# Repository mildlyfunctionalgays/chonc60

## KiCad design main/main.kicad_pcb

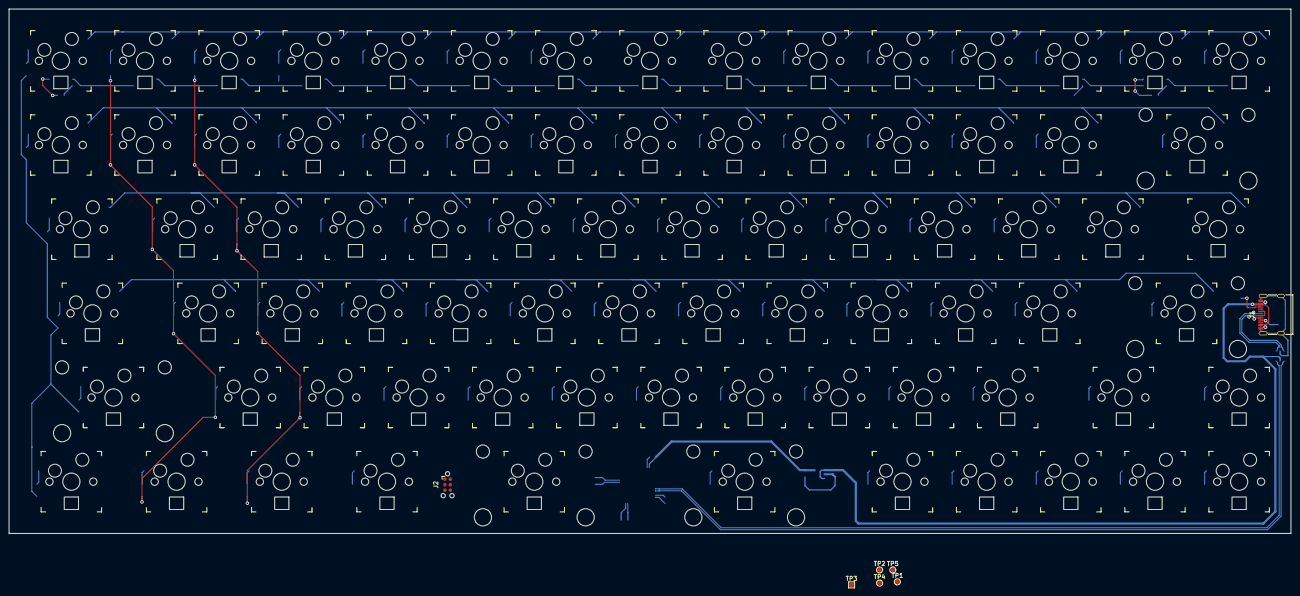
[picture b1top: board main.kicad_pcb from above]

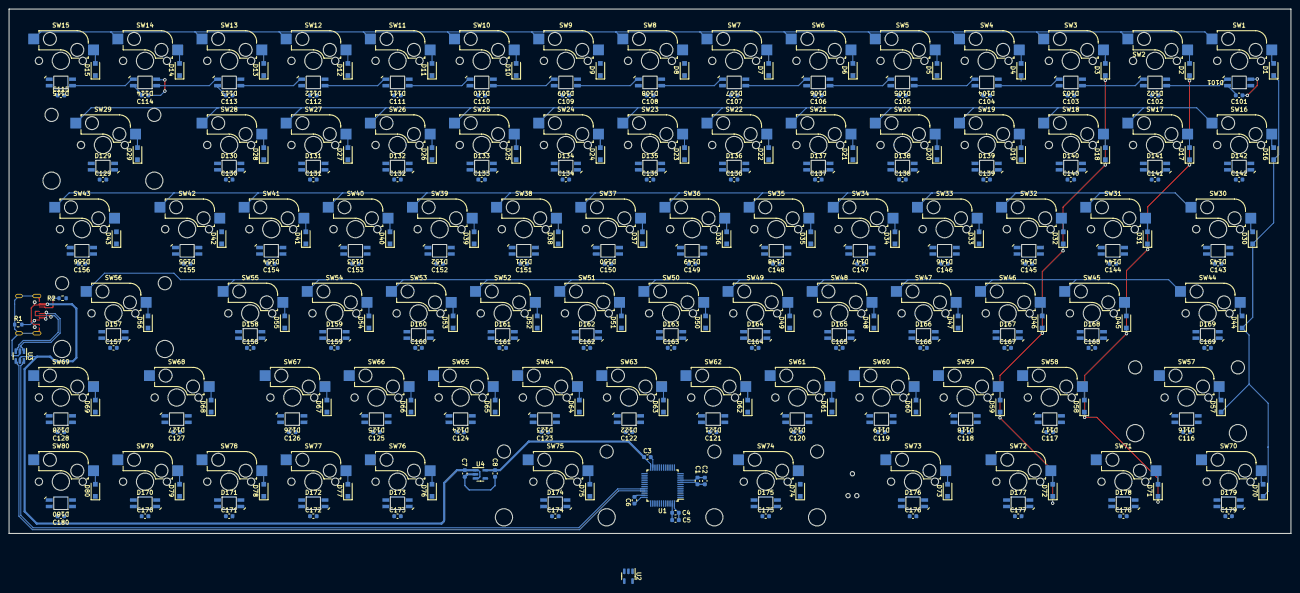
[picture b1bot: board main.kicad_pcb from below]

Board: 2 copper layers, 297.0 x 121.5 mm, 341 parts (254 on the bottom side), 195 nets.

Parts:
C1, C3, C4, C6, C101, C102, C103, C104, C105, C106, C107, C108, C109, C110, C111, C112, C113, C114, C115, C116, C117, C118, C119, C120, C121, C122, C123, C124, C125, C126, C127, C128, C129, C130, C131, C132, C133, C134, C135, C136, C137, C138, C139, C140, C141, C142, C143, C144, C145, C146, C147, C148, C149, C150, C151, C152, C153, C154, C155, C156, C157, C158, C159, C160, C161, C162, C163, C164, C165, C166, C167, C168, C169, C170, C171, C172, C173, C174, C175, C176, C177, C178, C179, C180: 100nF; C_0603_1608Metric
C2, C7, C8: 1µF; C_0603_1608Metric
C5: 10µF; C_0603_1608Metric
D1, D2, D3, D4, D5, D6, D7, D8, D9, D10, D11, D12, D13, D14, D15, D16, D17, D18, D19, D20, D21, D22, D23, D24, D25, D26, D27, D28, D29, D30, D31, D32, D33, D34, D35, D36, D37, D38, D39, D40, D41, D42, D43, D44, D45, D46, D47, D48, D49, D50, D51, D52, D53, D54, D55, D56, D57, D58, D59, D60, D61, D62, D63, D64, D65, D66, D67, D68, D69, D70, D71, D72, D73, D74, D75, D76, D77, D78, D79, D80: D_Small; D_SOD-123F
D101, D102, D103, D104, D105, D106, D107, D108, D109, D110, D111, D112, D113, D114, D115, D116, D117, D118, D119, D120, D121, D122, D123, D124, D125, D126, D127, D128, D129, D130, D131, D132, D133, D134, D135, D136, D137, D138, D139, D140, D141, D142, D143, D144, D145, D146, D147, D148, D149, D150, D151, D152, D153, D154, D155, D156, D157, D158, D159, D160, D161, D162, D163, D164, D165, D166, D167, D168, D169, D170, D171, D172, D173, D174, D175, D176, D177, D178, D179, D180: SK6812MINI-E; LED_SK6812_MINI_E_REVERSE
J1: USB_C_Receptacle_USB2.0; USB_C_Receptacle_JING_C167321
J2: TC2030_SWD; Tag-Connect_TC2030-IDC-NL_2x03_P1.27mm_Vertical
R1, R2: 5.1kΩ; R_0603_1608Metric
SW1, SW2, SW3, SW4, SW5, SW6, SW7, SW8, SW9, SW10, SW11, SW12, SW13, SW14, SW15, SW16, SW17, SW18, SW19, SW20, SW21, SW22, SW23, SW24, SW25, SW26, SW27, SW28, SW29, SW30, SW31, SW32, SW33, SW34, SW35, SW36, SW37, SW38, SW39, SW40, SW41, SW42, SW43, SW44, SW45, SW46, SW47, SW48, SW49, SW50, SW51, SW52, SW53, SW54, SW55, SW56, SW57, SW58, SW59, SW60, SW61, SW62, SW63, SW64, SW65, SW66, SW67, SW68, SW69, SW70, SW71, SW72, SW73, SW74, SW75, SW76, SW77, SW78, SW79, SW80: SW_Push_45deg; Kailh_socket_MX
TP1: BOOT0; TestPoint_Pad_D1.0mm
TP2: ~RESET; TestPoint_Pad_D1.0mm
TP3: GND; TestPoint_Pad_1.0x1.0mm
TP4: 5V; TestPoint_Pad_D1.0mm
TP5: 3V3; TestPoint_Pad_D1.0mm
U1: STM32L063C8Tx; LQFP-48_7x7mm_P0.5mm
U2: SN74LV1T34DBV; SOT-23-5
U3: WE-TVS-82400102; SOT-23-6
U4: MIC5504-3.3YMT; SOT-23-5

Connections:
+3V3: C1.1, C2.1, C3.1, C4.1, C5.1, C6.1, C8.1, J2.5 (GND), TP5.1, U1.9 (VDDA), U1.24 (VDD), U1.36 (VDD_USB), U1.48 (VDD), U4.5 (VOUT)
+5V: C7.1, C101.2, C102.2, C103.2, C104.2, C105.2, C106.2, C107.2, C108.2, C109.2, C110.2, C111.2, C112.2, C113.2, C114.2, C115.2, C116.2, C117.2, C118.2, C119.2, C120.2, C121.2, C122.2, C123.2, C124.2, C125.2, C126.2, C127.2, C128.2, C129.2, C130.2, C131.2, C132.2, C133.2, C134.2, C135.2, C136.2, C137.2, C138.2, C139.2, C140.2, C141.2, C142.2, C143.2, C144.2, C145.2, C146.2, C147.2, C148.2, C149.2, C150.2, C151.2, C152.2, C153.2, C154.2, C155.2, C156.2, C157.2, C158.2, C159.2, C160.2, C161.2, C162.2, C163.2, C164.2, C165.2, C166.2, C167.2, C168.2, C169.2, C170.2, C171.2, C172.2, C173.2, C174.2, C175.2, C176.2, C177.2, C178.2, C179.2, C180.2, D101.1 (VDD), D102.1 (VDD), D103.1 (VDD), D104.1 (VDD), D105.1 (VDD), D106.1 (VDD), D107.1 (VDD), D108.1 (VDD), D109.1 (VDD), D110.1 (VDD), D111.1 (VDD), D112.1 (VDD), D113.1 (VDD), D114.1 (VDD), D115.1 (VDD), D116.1 (VDD), D117.1 (VDD), D118.1 (VDD), D119.1 (VDD), D120.1 (VDD), D121.1 (VDD), D122.1 (VDD), D123.1 (VDD), D124.1 (VDD), D125.1 (VDD), D126.1 (VDD), D127.1 (VDD), D128.1 (VDD), D129.1 (VDD), D130.1 (VDD), D131.1 (VDD), D132.1 (VDD), D133.1 (VDD), D134.1 (VDD), D135.1 (VDD), D136.1 (VDD), D137.1 (VDD), D138.1 (VDD), D139.1 (VDD), D140.1 (VDD), D141.1 (VDD), D142.1 (VDD), D143.1 (VDD), D144.1 (VDD), D145.1 (VDD), D146.1 (VDD), D147.1 (VDD), D148.1 (VDD), D149.1 (VDD), D150.1 (VDD), D151.1 (VDD), D152.1 (VDD), D153.1 (VDD), D154.1 (VDD), D155.1 (VDD), D156.1 (VDD), D157.1 (VDD), D158.1 (VDD), D159.1 (VDD), D160.1 (VDD), D161.1 (VDD), D162.1 (VDD), D163.1 (VDD), D164.1 (VDD), D165.1 (VDD), D166.1 (VDD), D167.1 (VDD), D168.1 (VDD), D169.1 (VDD), D170.1 (VDD), D171.1 (VDD), D172.1 (VDD), D173.1 (VDD), D174.1 (VDD), D175.1 (VDD), D176.1 (VDD), D177.1 (VDD), D178.1 (VDD), D179.1 (VDD), D180.1 (VDD), J1.A4 (VBUS), J1.A9 (VBUS), J1.B4 (VBUS), J1.B9 (VBUS), TP4.1, U2.5 (VCC), U3.5, U4.1 (VIN), U4.3 (EN)
/C_D+: J1.A6 (D+), J1.B6 (D+), U3.3
/C_D-: J1.A7 (D-), J1.B7 (D-), U3.1
/Keyswitches/COL0: D1.1 (K), D16.1 (K), D30.1 (K), D44.1 (K), D57.1 (K), D70.1 (K), U1.10 (PA0)
/Keyswitches/COL1: D2.1 (K), D17.1 (K), D31.1 (K), D45.1 (K), D58.1 (K), D71.1 (K), U1.11 (PA1)
/Keyswitches/COL2: D3.1 (K), D18.1 (K), D32.1 (K), D46.1 (K), D59.1 (K), D72.1 (K), U1.12 (PA2)
/Keyswitches/COL3: D4.1 (K), D19.1 (K), D33.1 (K), D47.1 (K), D60.1 (K), D73.1 (K), U1.13 (PA3)
/Keyswitches/COL4: D5.1 (K), D20.1 (K), D34.1 (K), D48.1 (K), D61.1 (K), D74.1 (K), U1.14 (PA4)
/Keyswitches/COL5: D6.1 (K), D21.1 (K), D35.1 (K), D49.1 (K), D62.1 (K), U1.15 (PA5)
/Keyswitches/COL6: D7.1 (K), D22.1 (K), D36.1 (K), D50.1 (K), D63.1 (K), U1.16 (PA6)
/Keyswitches/COL7: D8.1 (K), D23.1 (K), D37.1 (K), D51.1 (K), D64.1 (K), D75.1 (K), U1.17 (PA7)
/Keyswitches/COL8: D9.1 (K), D24.1 (K), D38.1 (K), D52.1 (K), D65.1 (K), U1.18 (PB0)
/Keyswitches/COL9: D10.1 (K), D25.1 (K), D39.1 (K), D53.1 (K), U1.19 (PB1)
/Keyswitches/COL10: D11.1 (K), D26.1 (K), D40.1 (K), D76.1 (K), U1.20 (PB2)
/Keyswitches/COL11: D12.1 (K), D27.1 (K), D41.1 (K), D54.1 (K), D66.1 (K), D77.1 (K), U1.21 (PB10)
/Keyswitches/COL12: D13.1 (K), D28.1 (K), D42.1 (K), D55.1 (K), D67.1 (K), D78.1 (K), U1.22 (PB11)
/Keyswitches/COL13: D14.1 (K), D29.1 (K), D43.1 (K), D56.1 (K), D68.1 (K), D79.1 (K), U1.25 (PB12)
/Keyswitches/COL14: D15.1 (K), D69.1 (K), D80.1 (K), U1.26 (PB13)
/Keyswitches/ROW0: SW1.1, SW2.1, SW3.1, SW4.1, SW5.1, SW6.1, SW7.1, SW8.1, SW9.1, SW10.1, SW11.1, SW12.1, SW13.1, SW14.1, SW15.1, U1.40 (PB4)
/Keyswitches/ROW1: SW16.1, SW17.1, SW18.1, SW19.1, SW20.1, SW21.1, SW22.1, SW23.1, SW24.1, SW25.1, SW26.1, SW27.1, SW28.1, SW29.1, U1.41 (PB5)
/Keyswitches/ROW2: SW30.1, SW31.1, SW32.1, SW33.1, SW34.1, SW35.1, SW36.1, SW37.1, SW38.1, SW39.1, SW40.1, SW41.1, SW42.1, SW43.1, U1.42 (PB6)
/Keyswitches/ROW3: SW44.1, SW45.1, SW46.1, SW47.1, SW48.1, SW49.1, SW50.1, SW51.1, SW52.1, SW53.1, SW54.1, SW55.1, SW56.1, U1.43 (PB7)
/Keyswitches/ROW4: SW57.1, SW58.1, SW59.1, SW60.1, SW61.1, SW62.1, SW63.1, SW64.1, SW65.1, SW66.1, SW67.1, SW68.1, SW69.1, U1.45 (PB8)
/Keyswitches/ROW5: SW70.1, SW71.1, SW72.1, SW73.1, SW74.1, SW75.1, SW76.1, SW77.1, SW78.1, SW79.1, SW80.1, U1.46 (PB9)
/MCU_DOUT: U1.28 (PB15), U2.2 (A)
/Row 0/LED_IN: D101.4 (DIN), U2.4 (Y)
/Row 0/LED_OUT: D115.2 (DOUT), D129.4 (DIN)
/Row 1/LED_OUT: D142.2 (DOUT), D143.4 (DIN)
/Row 2/LED_OUT: D156.2 (DOUT), D157.4 (DIN)
/Row 3/LED_OUT: D116.4 (DIN), D169.2 (DOUT)
/Row 4/LED_OUT: D128.2 (DOUT), D170.4 (DIN)
/SWCLK: J2.3 (~RESET), U1.37 (PA14)
/SWDIO: J2.6 (SWO), U1.34 (PA13)
/USB_D+: U1.33 (PA12), U3.4
/USB_D-: U1.32 (PA11), U3.6
/~RESET: J2.4 (SWCLK), TP2.1, U1.7 (NRST)
GND: C1.2, C2.2, C3.2, C4.2, C5.2, C6.2, C7.2, C8.2, C101.1, C102.1, C103.1, C104.1, C105.1, C106.1, C107.1, C108.1, C109.1, C110.1, C111.1, C112.1, C113.1, C114.1, C115.1, C116.1, C117.1, C118.1, C119.1, C120.1, C121.1, C122.1, C123.1, C124.1, C125.1, C126.1, C127.1, C128.1, C129.1, C130.1, C131.1, C132.1, C133.1, C134.1, C135.1, C136.1, C137.1, C138.1, C139.1, C140.1, C141.1, C142.1, C143.1, C144.1, C145.1, C146.1, C147.1, C148.1, C149.1, C150.1, C151.1, C152.1, C153.1, C154.1, C155.1, C156.1, C157.1, C158.1, C159.1, C160.1, C161.1, C162.1, C163.1, C164.1, C165.1, C166.1, C167.1, C168.1, C169.1, C170.1, C171.1, C172.1, C173.1, C174.1, C175.1, C176.1, C177.1, C178.1, C179.1, C180.1, D101.3 (GND), D102.3 (GND), D103.3 (GND), D104.3 (GND), D105.3 (GND), D106.3 (GND), D107.3 (GND), D108.3 (GND), D109.3 (GND), D110.3 (GND), D111.3 (GND), D112.3 (GND), D113.3 (GND), D114.3 (GND), D115.3 (GND), D116.3 (GND), D117.3 (GND), D118.3 (GND), D119.3 (GND), D120.3 (GND), D121.3 (GND), D122.3 (GND), D123.3 (GND), D124.3 (GND), D125.3 (GND), D126.3 (GND), D127.3 (GND), D128.3 (GND), D129.3 (GND), D130.3 (GND), D131.3 (GND), D132.3 (GND), D133.3 (GND), D134.3 (GND), D135.3 (GND), D136.3 (GND), D137.3 (GND), D138.3 (GND), D139.3 (GND), D140.3 (GND), D141.3 (GND), D142.3 (GND), D143.3 (GND), D144.3 (GND), D145.3 (GND), D146.3 (GND), D147.3 (GND), D148.3 (GND), D149.3 (GND), D150.3 (GND), D151.3 (GND), D152.3 (GND), D153.3 (GND), D154.3 (GND), D155.3 (GND), D156.3 (GND), D157.3 (GND), D158.3 (GND), D159.3 (GND), D160.3 (GND), D161.3 (GND), D162.3 (GND), D163.3 (GND), D164.3 (GND), D165.3 (GND), D166.3 (GND), D167.3 (GND), D168.3 (GND), D169.3 (GND), D170.3 (GND), D171.3 (GND), D172.3 (GND), D173.3 (GND), D174.3 (GND), D175.3 (GND), D176.3 (GND), D177.3 (GND), D178.3 (GND), D179.3 (GND), D180.3 (GND), J1.A1 (GND), J1.A12 (GND), J1.B1 (GND), J1.B12 (GND), J1.S1 (SHIELD), J2.1 (VCC), R1.2, R2.2, TP3.1, U1.8 (VSSA), U1.23 (VSS), U1.35 (VSS), U1.47 (VSS), U2.3 (GND), U3.2, U4.2 (GND)
unnamed: D1.2 (A), SW1.2
unnamed: D2.2 (A), SW2.2
unnamed: D3.2 (A), SW3.2
unnamed: D4.2 (A), SW4.2
unnamed: D5.2 (A), SW5.2
unnamed: D6.2 (A), SW6.2
unnamed: D7.2 (A), SW7.2
unnamed: D8.2 (A), SW8.2
unnamed: D9.2 (A), SW9.2
unnamed: D10.2 (A), SW10.2
unnamed: D11.2 (A), SW11.2
unnamed: D12.2 (A), SW12.2
unnamed: D13.2 (A), SW13.2
unnamed: D14.2 (A), SW14.2
unnamed: D15.2 (A), SW15.2
unnamed: D16.2 (A), SW16.2
unnamed: D17.2 (A), SW17.2
unnamed: D18.2 (A), SW18.2
unnamed: D19.2 (A), SW19.2
unnamed: D20.2 (A), SW20.2
unnamed: D21.2 (A), SW21.2
unnamed: D22.2 (A), SW22.2
unnamed: D23.2 (A), SW23.2
unnamed: D24.2 (A), SW24.2
unnamed: D25.2 (A), SW25.2
unnamed: D26.2 (A), SW26.2
unnamed: D27.2 (A), SW27.2
unnamed: D28.2 (A), SW28.2
unnamed: D29.2 (A), SW29.2
unnamed: D30.2 (A), SW30.2
unnamed: D31.2 (A), SW31.2
unnamed: D32.2 (A), SW32.2
unnamed: D33.2 (A), SW33.2
unnamed: D34.2 (A), SW34.2
unnamed: D35.2 (A), SW35.2
unnamed: D36.2 (A), SW36.2
unnamed: D37.2 (A), SW37.2
unnamed: D38.2 (A), SW38.2
unnamed: D39.2 (A), SW39.2
unnamed: D40.2 (A), SW40.2
unnamed: D41.2 (A), SW41.2
unnamed: D42.2 (A), SW42.2
unnamed: D43.2 (A), SW43.2
unnamed: D44.2 (A), SW44.2
unnamed: D45.2 (A), SW45.2
unnamed: D46.2 (A), SW46.2
unnamed: D47.2 (A), SW47.2
unnamed: D48.2 (A), SW48.2
unnamed: D49.2 (A), SW49.2
unnamed: D50.2 (A), SW50.2
unnamed: D51.2 (A), SW51.2
unnamed: D52.2 (A), SW52.2
unnamed: D53.2 (A), SW53.2
unnamed: D54.2 (A), SW54.2
unnamed: D55.2 (A), SW55.2
unnamed: D56.2 (A), SW56.2
unnamed: D57.2 (A), SW57.2
unnamed: D58.2 (A), SW58.2
unnamed: D59.2 (A), SW59.2
unnamed: D60.2 (A), SW60.2
unnamed: D61.2 (A), SW61.2
unnamed: D62.2 (A), SW62.2
unnamed: D63.2 (A), SW63.2
unnamed: D64.2 (A), SW64.2
unnamed: D65.2 (A), SW65.2
unnamed: D66.2 (A), SW66.2
unnamed: D67.2 (A), SW67.2
unnamed: D68.2 (A), SW68.2
unnamed: D69.2 (A), SW69.2
unnamed: D70.2 (A), SW70.2
unnamed: D71.2 (A), SW71.2
unnamed: D72.2 (A), SW72.2
unnamed: D73.2 (A), SW73.2
unnamed: D74.2 (A), SW74.2
unnamed: D75.2 (A), SW75.2
unnamed: D76.2 (A), SW76.2
unnamed: D77.2 (A), SW77.2
unnamed: D78.2 (A), SW78.2
unnamed: D79.2 (A), SW79.2
unnamed: D80.2 (A), SW80.2
unnamed: D101.2 (DOUT), D102.4 (DIN)
unnamed: D102.2 (DOUT), D103.4 (DIN)
unnamed: D103.2 (DOUT), D104.4 (DIN)
unnamed: D104.2 (DOUT), D105.4 (DIN)
unnamed: D105.2 (DOUT), D106.4 (DIN)
unnamed: D106.2 (DOUT), D107.4 (DIN)
unnamed: D107.2 (DOUT), D108.4 (DIN)
unnamed: D108.2 (DOUT), D109.4 (DIN)
unnamed: D109.2 (DOUT), D110.4 (DIN)
unnamed: D110.2 (DOUT), D111.4 (DIN)
unnamed: D111.2 (DOUT), D112.4 (DIN)
unnamed: D112.2 (DOUT), D113.4 (DIN)
unnamed: D113.2 (DOUT), D114.4 (DIN)
unnamed: D114.2 (DOUT), D115.4 (DIN)
unnamed: D116.2 (DOUT), D117.4 (DIN)
unnamed: D117.2 (DOUT), D118.4 (DIN)
unnamed: D118.2 (DOUT), D119.4 (DIN)
unnamed: D119.2 (DOUT), D120.4 (DIN)
unnamed: D120.2 (DOUT), D121.4 (DIN)
unnamed: D121.2 (DOUT), D122.4 (DIN)
unnamed: D122.2 (DOUT), D123.4 (DIN)
unnamed: D123.2 (DOUT), D124.4 (DIN)
unnamed: D124.2 (DOUT), D125.4 (DIN)
unnamed: D125.2 (DOUT), D126.4 (DIN)
unnamed: D126.2 (DOUT), D127.4 (DIN)
unnamed: D127.2 (DOUT), D128.4 (DIN)
unnamed: D129.2 (DOUT), D130.4 (DIN)
unnamed: D130.2 (DOUT), D131.4 (DIN)
unnamed: D131.2 (DOUT), D132.4 (DIN)
unnamed: D132.2 (DOUT), D133.4 (DIN)
unnamed: D133.2 (DOUT), D134.4 (DIN)
unnamed: D134.2 (DOUT), D135.4 (DIN)
unnamed: D135.2 (DOUT), D136.4 (DIN)
unnamed: D136.2 (DOUT), D137.4 (DIN)
unnamed: D137.2 (DOUT), D138.4 (DIN)
unnamed: D138.2 (DOUT), D139.4 (DIN)
unnamed: D139.2 (DOUT), D140.4 (DIN)
unnamed: D140.2 (DOUT), D141.4 (DIN)
unnamed: D141.2 (DOUT), D142.4 (DIN)
unnamed: D143.2 (DOUT), D144.4 (DIN)
unnamed: D144.2 (DOUT), D145.4 (DIN)
unnamed: D145.2 (DOUT), D146.4 (DIN)
unnamed: D146.2 (DOUT), D147.4 (DIN)
unnamed: D147.2 (DOUT), D148.4 (DIN)
unnamed: D148.2 (DOUT), D149.4 (DIN)
unnamed: D149.2 (DOUT), D150.4 (DIN)
unnamed: D150.2 (DOUT), D151.4 (DIN)
unnamed: D151.2 (DOUT), D152.4 (DIN)
unnamed: D152.2 (DOUT), D153.4 (DIN)
unnamed: D153.2 (DOUT), D154.4 (DIN)
unnamed: D154.2 (DOUT), D155.4 (DIN)
unnamed: D155.2 (DOUT), D156.4 (DIN)
unnamed: D157.2 (DOUT), D158.4 (DIN)
unnamed: D158.2 (DOUT), D159.4 (DIN)
unnamed: D159.2 (DOUT), D160.4 (DIN)
unnamed: D160.2 (DOUT), D161.4 (DIN)
unnamed: D161.2 (DOUT), D162.4 (DIN)
unnamed: D162.2 (DOUT), D163.4 (DIN)
unnamed: D163.2 (DOUT), D164.4 (DIN)
unnamed: D164.2 (DOUT), D165.4 (DIN)
unnamed: D165.2 (DOUT), D166.4 (DIN)
unnamed: D166.2 (DOUT), D167.4 (DIN)
unnamed: D167.2 (DOUT), D168.4 (DIN)
unnamed: D168.2 (DOUT), D169.4 (DIN)
unnamed: D170.2 (DOUT), D171.4 (DIN)
unnamed: D171.2 (DOUT), D172.4 (DIN)
unnamed: D172.2 (DOUT), D173.4 (DIN)
unnamed: D173.2 (DOUT), D174.4 (DIN)
unnamed: D174.2 (DOUT), D175.4 (DIN)
unnamed: D175.2 (DOUT), D176.4 (DIN)
unnamed: D176.2 (DOUT), D177.4 (DIN)
unnamed: D177.2 (DOUT), D178.4 (DIN)
unnamed: D178.2 (DOUT), D179.4 (DIN)
unnamed: D179.2 (DOUT), D180.4 (DIN)
unnamed: J1.A5 (CC1), R1.1
unnamed: J1.B5 (CC2), R2.1
unnamed: TP1.1, U1.44 (BOOT0)

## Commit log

2021-04-28 Initial commit with atmega32u4
2021-05-03 Add proposed layout, start LEDs
2021-05-03 Initial schematic complete
2021-05-04 Start placing components
2021-05-04 Keyswitches placed
2021-05-05 Start placing diodes
2021-05-05 Place diodes
2021-05-05 Place LEDs, start routing
2021-05-14 Make LEDs make more sense, with automation!
2021-05-16 Update to new keyboard layout
2021-05-17 Move around parts, some matrix routing
2021-05-19 Switch to STM32L063 because I can actually buy those
2021-05-22 Route all rows and columns in the matrix
2021-05-22 Fix diode positioning and nets
2021-05-22 Most routing done
2021-05-23 No more ratsnest
2021-05-25 Start appeasing the DRC
2022-01-26 Convert to kicad 6.0
2022-02-05 Switch to nRF58420 module and battery power
2022-02-05 Start updating PCB for new design
2022-02-22 routing work
2022-03-10 Remove wat.py
2022-03-10 Connect up MCU
2022-03-10 Connect power managment to MCU
    i don't like it but hopefully it will work

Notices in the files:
parts and their libraries:
License: This symbol is based off of the SK6812 official KiCad symbol and is thus under its modified CC-BY-SA 4.0 license instead of MIT
